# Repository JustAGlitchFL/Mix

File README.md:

# Mix
A multipurpose audio-focused console

## Why
I find myself constantly tuning my audio mix from different apps through windows, and would like a panel to adjust levels on the fly. I also wanted to use this for mixing audio for music and video projects, so I included 8 channels. Each channel has a slider for feed volume, an encoder for monitoring volume, a solo button, and a mute button. Everything is remappable to select functions for your usecase. I also included 2 neopixels per channel, one for status, and one for leveling by color.

## Assembly
Like [Timeline](https://github.com/justaglitchfl/timeline), ~~no case for this one~~ CASE FILES AVAILABLE NOW, as I want that raw PCB aesthetic. Solder everything together, good luck with the SMD for the ADC and IO expander! Might do a case when I get to uni and have access to actually functional printers if I get tired of the pcb as is. As with my other projects recently, drop some 3M 2229 on the back to protect it/the table, and to keep it in place (I love this stuff).

## BOM
|q  |part                          |link                                                                                                                                                                                                                                                                                                                                                                                                                                                                                                                |price       |total  |
|---|------------------------------|--------------------------------------------------------------------------------------------------------------------------------------------------------------------------------------------------------------------------------------------------------------------------------------------------------------------------------------------------------------------------------------------------------------------------------------------------------------------------------------------------------------------|------------|-------|
|1  |pcb                           |                                                                                                                                                                                                                                                                                                                                                                                                                                                                                                                    |$42.60      |$128.78|
|16 |switches                      |https://www.amazon.com/Kailh-Box-Switches-Mechanical-Keyboards/dp/B09WYVJ4F9/ref=sr_1_6?crid=2BTWSUBF3M8FT&dib=eyJ2IjoiMSJ9.E7vTxhYXmILeUbyObROhU1-pIkGjrufbSlMHAIG1e1llnfgUb6kJH0aZrhKnghy3-ae39fOUC746uLoqyr3XWC62Htlj0ggtZ9ec4c0ypx7s1OXmhTfKQ-o2rJuyfk5aXhqV22nhrib2PZU7WaA4AQrzeExJuEfAlETDZ-vuRMSWAneuQMiuWeqVX5Q3DunrHOugdER5ro68nIeODJWdx1rM1AFtYghjvFvBt4W0Gkk.dJo-mbx2UtVbx1mbN98GCLOOPWtmLr-b0G6qjvDffpM&dib_tag=se&keywords=kailh%2Bbox%2Bjade&qid=1754458378&sprefix=kailh%2Bbo%2Caps%2C137&sr=8-6&th=1|$25.98      |       |
|8  |ECE11                         |https://lcsc.com/product-detail/Rotary-Encoders_ALPSALPINE-EC11E18244AU_C202365.html                                                                                                                                                                                                                                                                                                                                                                                                                                |$15.71      |       |
|8  |slide potentiometer           |https://lcsc.com/product-detail/Potentiometers-Variable-Resistors_BOURNS-PTA4543-2015DPB103_C17444183.html?s_z=n_%25C2%25B120%2525%2520250mW%252010k%25CE%25A9%2520Through%2520Hole%2520Potentiometers%252C%2520Variable%2520Resistors%2520ROHS                                                                                                                                                                                                                                                                     |$14.16      |       |
|1  |MCP23017_SO                   |https://lcsc.com/product-detail/I-O-Expanders_MICROCHIP-MCP23017T-E-SO_C629440.html?s_z=n_MCP23017_SO                                                                                                                                                                                                                                                                                                                                                                                                               |$1.94       |       |
|1  |MCP3008                       |https://lcsc.com/product-detail/Analog-to-Digital-Converters-ADC_MICROCHIP-MCP3008T-I-SL_C2651321.html?s_z=n_mcp3008                                                                                                                                                                                                                                                                                                                                                                                                |$3.30       |       |
|16 |0805 signal diode             |                                                                                                                                                                                                                                                                                                                                                                                                                                                                                                                    |have on hand|       |
|16 |sk6812 mini e                 |                                                                                                                                                                                                                                                                                                                                                                                                                                                                                                                    |have on hand|       |
|1  |pi pico usbc (i wan orph pico)|https://www.aliexpress.us/item/3256807183354679.html?spm=a2g0o.productlist.main.5.7a7f3de52hAPEA&algo_pvid=1f0d5b04-b26a-48e7-9a46-02294e034b27&algo_exp_id=1f0d5b04-b26a-48e7-9a46-02294e034b27-4&pdp_ext_f=%7B%22order%22%3A%2284%22%2C%22eval%22%3A%221%22%7D&pdp_npi=4%40dis%21USD%212.56%212.56%21%21%212.56%212.56%21%402101ef5e17540194226302590e807a%2112000040462155654%21sea%21US%216129401916%21X&curPageLogUid=bwr0jMqPdQNe&utparam-url=scene%3Asearch%7Cquery_from%3A                                  |$3.56       |       |
|1  |lcsc s+h                      |                                                                                                                                                                                                                                                                                                                                                                                                                                                                                                                    |$21.53      |       |

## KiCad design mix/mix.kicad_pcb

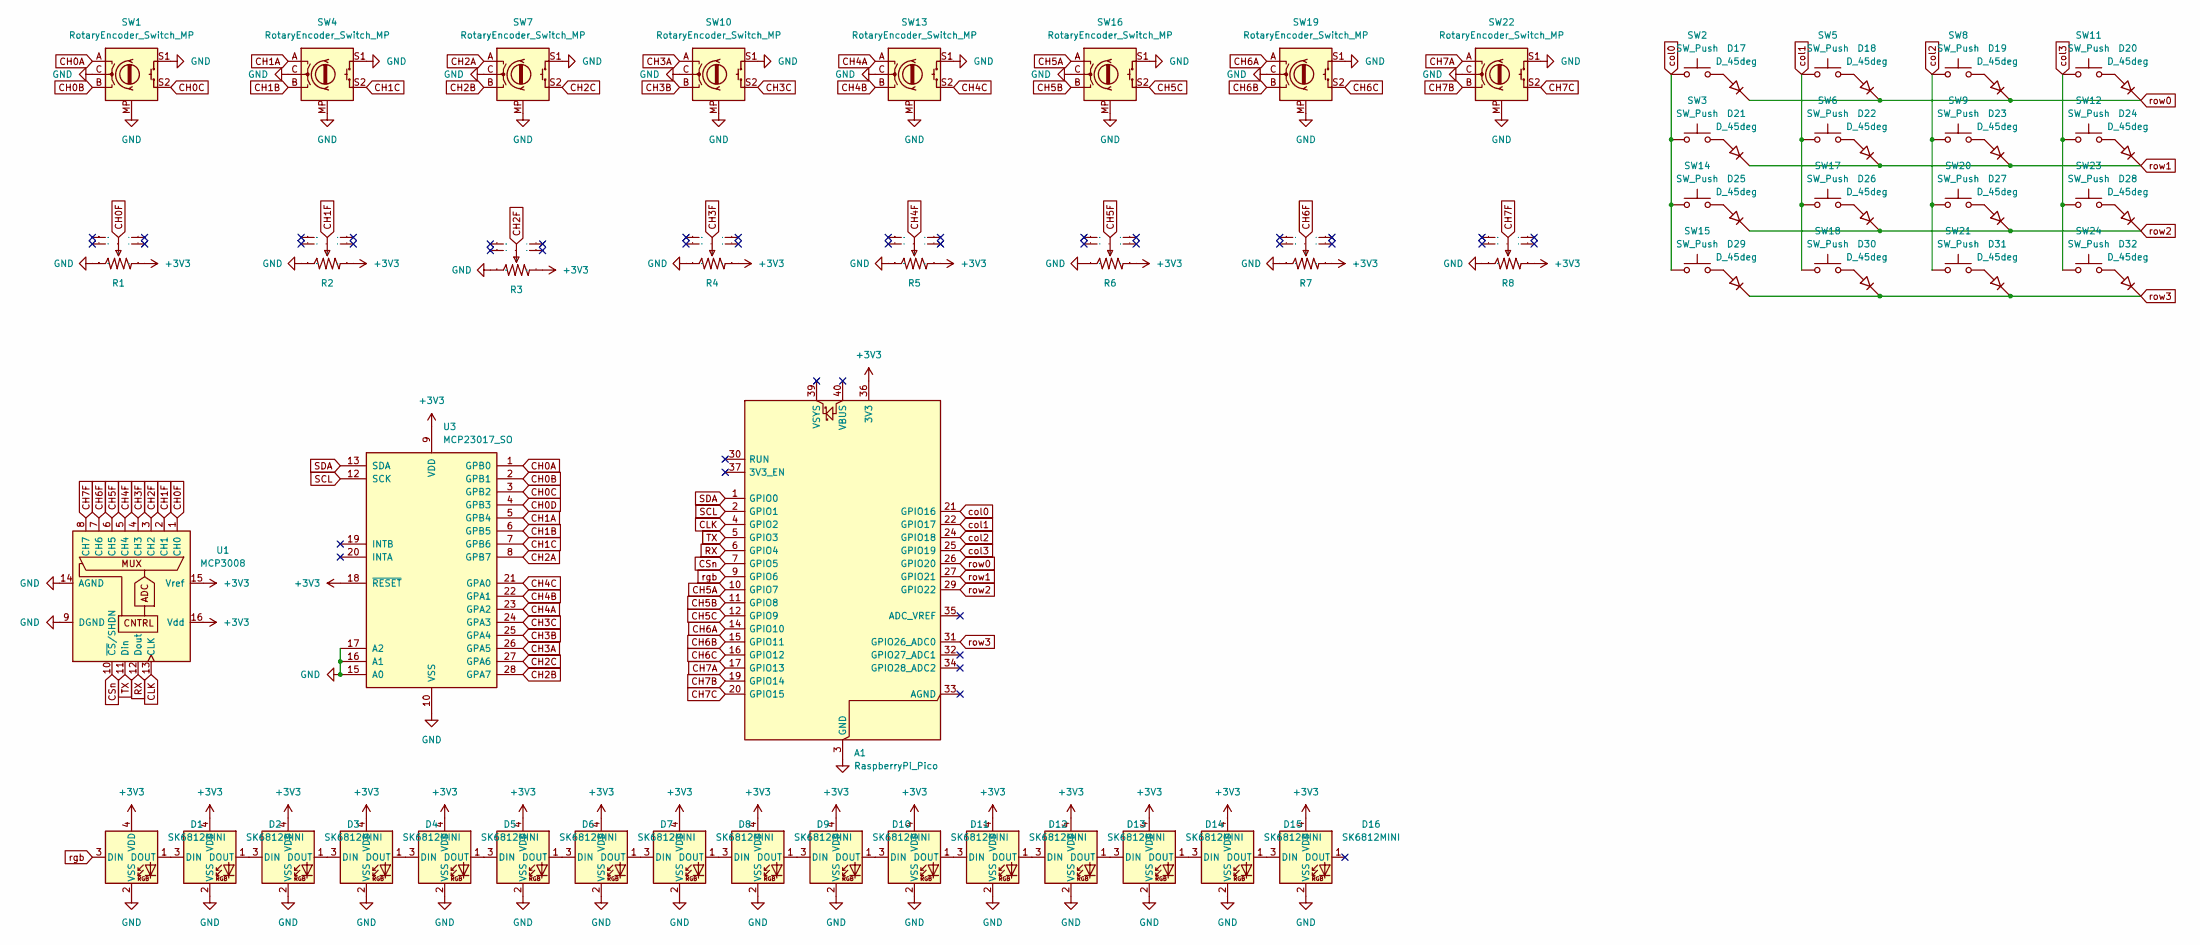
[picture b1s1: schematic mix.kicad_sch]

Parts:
A1: RaspberryPi_Pico; RaspberryPi_Pico_Common_Unspecified
D1, D2, D3, D4, D5, D6, D7, D8, D9, D10, D11, D12, D13, D14, D15, D16: SK6812MINI; SK6812MINI-E
D17, D18, D19, D20, D21, D22, D23, D24, D25, D26, D27, D28, D29, D30, D31, D32: D_45deg; D_0805_2012Metric_Pad1.15x1.40mm_HandSolder
R1, R2, R3, R4, R5, R6, R7, R8: RES-ADJ_PTA4543-2015CPB102
SW1, SW4, SW7, SW10, SW13, SW16, SW19, SW22: RotaryEncoder_Switch_MP; RotaryEncoder_Alps_EC11E-Switch_Vertical_H20mm_MountingHoles
SW2, SW3, SW5, SW6, SW8, SW9, SW11, SW12, SW14, SW15, SW17, SW18, SW20, SW21, SW23, SW24: SW_Push; SW_Cherry_MX_1.00u_PCB
U1: MCP3008; SOIC-16_3.9x9.9mm_P1.27mm
U3: MCP23017_SO; SOIC-28W_7.5x17.9mm_P1.27mm

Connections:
+3V3: A1.36 (3V3), D1.4 (VDD), D2.4 (VDD), D3.4 (VDD), D4.4 (VDD), D5.4 (VDD), D6.4 (VDD), D7.4 (VDD), D8.4 (VDD), D9.4 (VDD), D10.4 (VDD), D11.4 (VDD), D12.4 (VDD), D13.4 (VDD), D14.4 (VDD), D15.4 (VDD), D16.4 (VDD), R1.3, R2.3, R3.3, R4.3, R5.3, R6.3, R7.3, R8.3, U1.15 (Vref), U1.16 (Vdd), U3.9 (VDD), U3.18 (~RESET)
CH0A: SW1.A, U3.1 (GPB0)
CH0B: SW1.B, U3.2 (GPB1)
CH0C: SW1.S2, U3.3 (GPB2)
CH0D: U3.4 (GPB3)
CH0F: R1.2, U1.1 (CH0)
CH1A: SW4.A, U3.5 (GPB4)
CH1B: SW4.B, U3.6 (GPB5)
CH1C: SW4.S2, U3.7 (GPB6)
CH1F: R2.2, U1.2 (CH1)
CH2A: SW7.A, U3.8 (GPB7)
CH2B: SW7.B, U3.28 (GPA7)
CH2C: SW7.S2, U3.27 (GPA6)
CH2F: R3.2, U1.3 (CH2)
CH3A: SW10.A, U3.26 (GPA5)
CH3B: SW10.B, U3.25 (GPA4)
CH3C: SW10.S2, U3.24 (GPA3)
CH3F: R4.2, U1.4 (CH3)
CH4A: SW13.A, U3.23 (GPA2)
CH4B: SW13.B, U3.22 (GPA1)
CH4C: SW13.S2, U3.21 (GPA0)
CH4F: R5.2, U1.5 (CH4)
CH5A: A1.10 (GPIO7), SW16.A
CH5B: A1.11 (GPIO8), SW16.B
CH5C: A1.12 (GPIO9), SW16.S2
CH5F: R6.2, U1.6 (CH5)
CH6A: A1.14 (GPIO10), SW19.A
CH6B: A1.15 (GPIO11), SW19.B
CH6C: A1.16 (GPIO12), SW19.S2
CH6F: R7.2, U1.7 (CH6)
CH7A: A1.17 (GPIO13), SW22.A
CH7B: A1.19 (GPIO14), SW22.B
CH7C: A1.20 (GPIO15), SW22.S2
CH7F: R8.2, U1.8 (CH7)
CLK: A1.4 (GPIO2), U1.13 (CLK)
CSn: A1.7 (GPIO5), U1.10 (~CS/SHDN)
GND: A1.3 (GND), A1.8 (GND), A1.13 (GND), A1.18 (GND), A1.23 (GND), A1.28 (GND), A1.38 (GND), D1.2 (VSS), D2.2 (VSS), D3.2 (VSS), D4.2 (VSS), D5.2 (VSS), D6.2 (VSS), D7.2 (VSS), D8.2 (VSS), D9.2 (VSS), D10.2 (VSS), D11.2 (VSS), D12.2 (VSS), D13.2 (VSS), D14.2 (VSS), D15.2 (VSS), D16.2 (VSS), R1.1, R2.1, R3.1, R4.1, R5.1, R6.1, R7.1, R8.1, SW1.C, SW1.MP, SW1.S1, SW4.C, SW4.MP, SW4.S1, SW7.C, SW7.MP, SW7.S1, SW10.C, SW10.MP, SW10.S1, SW13.C, SW13.MP, SW13.S1, SW16.C, SW16.MP, SW16.S1, SW19.C, SW19.MP, SW19.S1, SW22.C, SW22.MP, SW22.S1, U1.9 (DGND), U1.14 (AGND), U3.10 (VSS), U3.15 (A0), U3.16 (A1), U3.17 (A2)
unnamed: D1.1 (DOUT), D2.3 (DIN)
unnamed: D2.1 (DOUT), D3.3 (DIN)
unnamed: D3.1 (DOUT), D4.3 (DIN)
unnamed: D4.1 (DOUT), D5.3 (DIN)
unnamed: D5.1 (DOUT), D6.3 (DIN)
unnamed: D6.1 (DOUT), D7.3 (DIN)
unnamed: D7.1 (DOUT), D8.3 (DIN)
unnamed: D8.1 (DOUT), D9.3 (DIN)
unnamed: D9.1 (DOUT), D10.3 (DIN)
unnamed: D10.1 (DOUT), D11.3 (DIN)
unnamed: D11.1 (DOUT), D12.3 (DIN)
unnamed: D12.1 (DOUT), D13.3 (DIN)
unnamed: D13.1 (DOUT), D14.3 (DIN)
unnamed: D14.1 (DOUT), D15.3 (DIN)
unnamed: D15.1 (DOUT), D16.3 (DIN)
unnamed: D17.2 (A), SW2.2
unnamed: D18.2 (A), SW5.2
unnamed: D19.2 (A), SW8.2
unnamed: D20.2 (A), SW11.2
unnamed: D21.2 (A), SW3.2
unnamed: D22.2 (A), SW6.2
unnamed: D23.2 (A), SW9.2
unnamed: D24.2 (A), SW12.2
unnamed: D25.2 (A), SW14.2
unnamed: D26.2 (A), SW17.2
unnamed: D27.2 (A), SW20.2
unnamed: D28.2 (A), SW23.2
unnamed: D29.2 (A), SW15.2
unnamed: D30.2 (A), SW18.2
unnamed: D31.2 (A), SW21.2
unnamed: D32.2 (A), SW24.2
RX: A1.6 (GPIO4), U1.12 (Dout)
SCL: A1.2 (GPIO1), U3.12 (SCK)
SDA: A1.1 (GPIO0), U3.13 (SDA)
TX: A1.5 (GPIO3), U1.11 (Din)
col0: A1.21 (GPIO16), SW2.1, SW3.1, SW14.1, SW15.1
col1: A1.22 (GPIO17), SW5.1, SW6.1, SW17.1, SW18.1
col2: A1.24 (GPIO18), SW8.1, SW9.1, SW20.1, SW21.1
col3: A1.25 (GPIO19), SW11.1, SW12.1, SW23.1, SW24.1
rgb: A1.9 (GPIO6), D1.3 (DIN)
row0: A1.26 (GPIO20), D17.1 (K), D18.1 (K), D19.1 (K), D20.1 (K)
row1: A1.27 (GPIO21), D21.1 (K), D22.1 (K), D23.1 (K), D24.1 (K)
row2: A1.29 (GPIO22), D25.1 (K), D26.1 (K), D27.1 (K), D28.1 (K)
row3: A1.31 (GPIO26_ADC0), D29.1 (K), D30.1 (K), D31.1 (K), D32.1 (K)

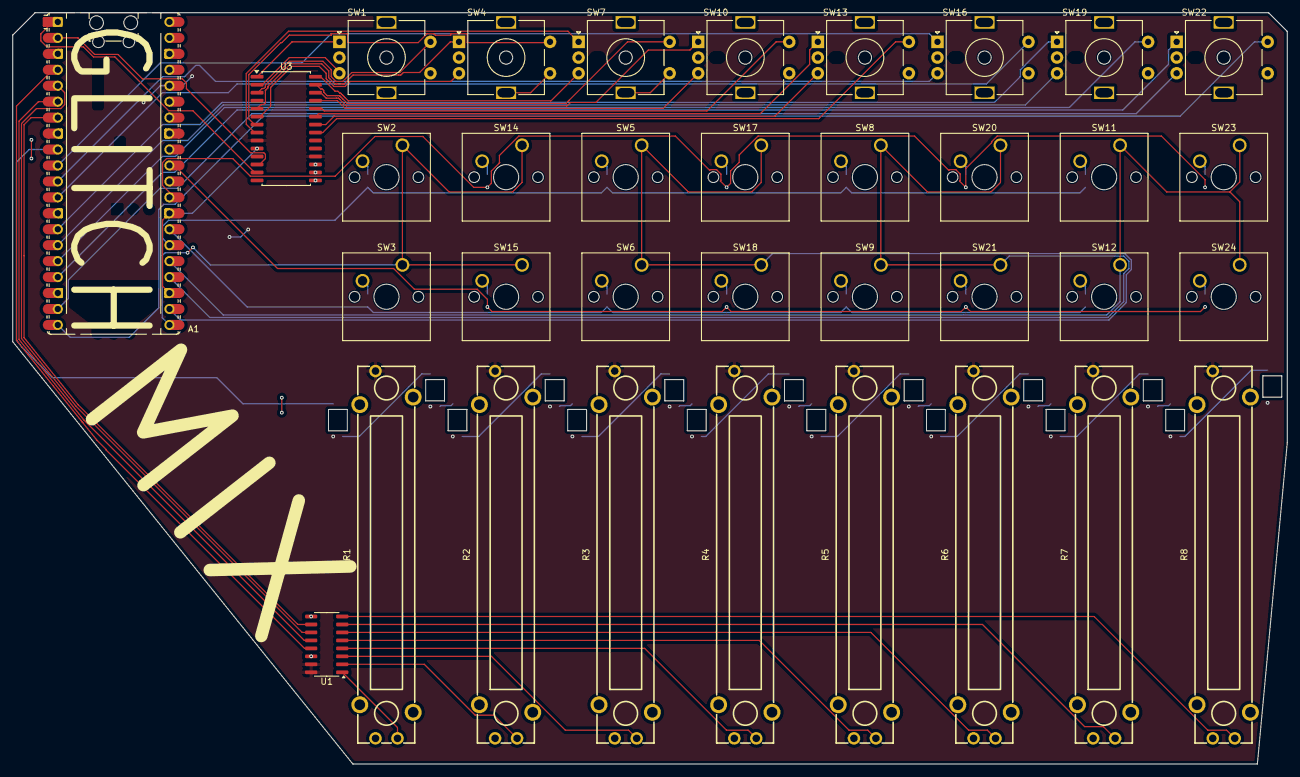
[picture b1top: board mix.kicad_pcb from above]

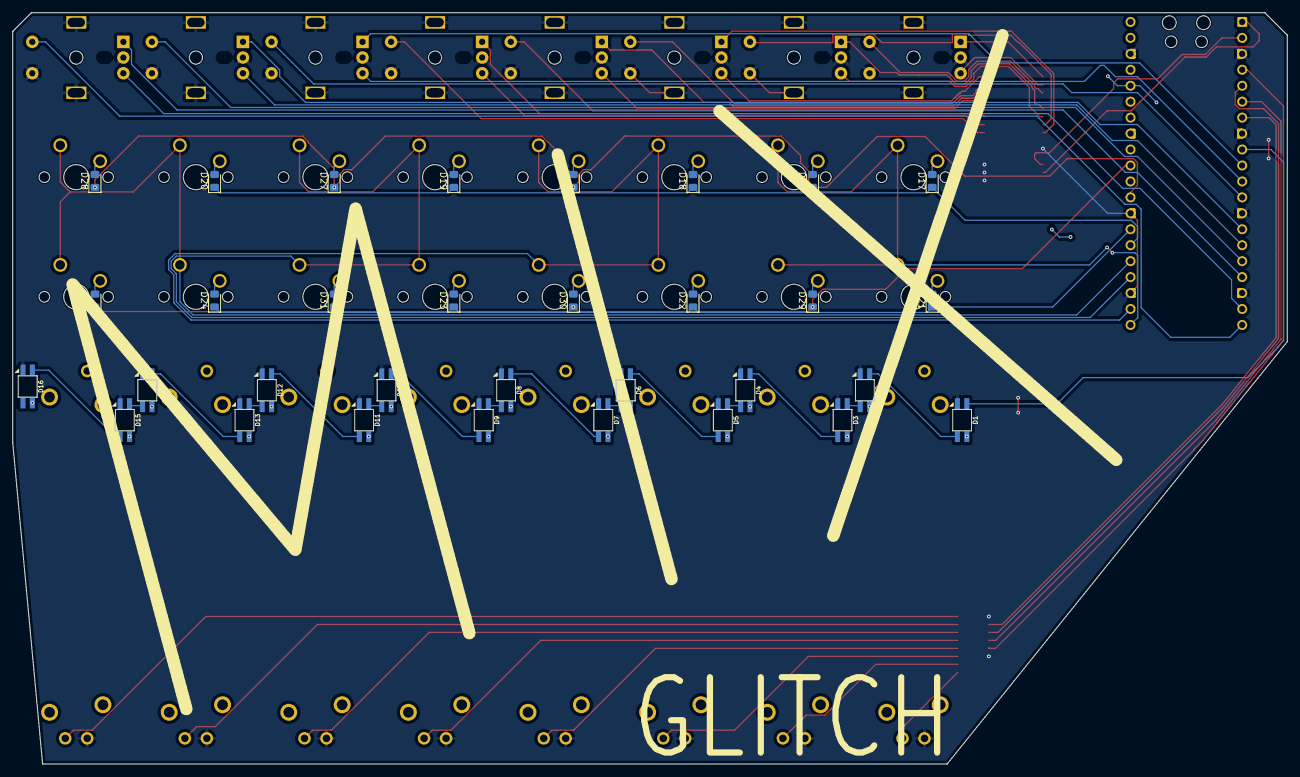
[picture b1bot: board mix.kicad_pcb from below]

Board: 2 copper layers, 202.9 x 119.6 mm, 67 parts (32 on the bottom side), 80 nets.

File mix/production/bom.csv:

Designator,Footprint,Quantity,Value,LCSC Part #
A1,RaspberryPi_Pico_Common_Unspecified,1,RaspberryPi_Pico,
"D1, D10, D11, D12, D13, D14, D15, D16, D2, D3, D4, D5, D6, D7, D8, D9",SK6812MINI-E,16,SK6812MINI,
"D17, D18, D19, D20, D21, D22, D23, D24, D25, D26, D27, D28, D29, D30, D31, D32",0805,16,D_45deg,
"R1, R2, R3, R4, R5, R6, R7, R8",RES-ADJ_PTA4543-2015CPB102,8,~,
"SW1, SW10, SW13, SW16, SW19, SW22, SW4, SW7",RotaryEncoder_Alps_EC11E-Switch_Vertical_H20mm_MountingHoles,8,RotaryEncoder_Switch_MP,
"SW11, SW12, SW14, SW15, SW17, SW18, SW2, SW20, SW21, SW23, SW24, SW3, SW5, SW6, SW8, SW9",SW_Cherry_MX_1.00u_PCB,16,SW_Push,
U1,SOIC-16_3.9x9.9mm_P1.27mm,1,MCP3008,
U3,SOIC-28W_7.5x17.9mm_P1.27mm,1,MCP23017_SO,

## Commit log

2025-07-21 sync
2025-07-22 jgfk;j
2025-08-01 images
2025-08-04 firmware
2025-08-06 case+fw
2025-08-06 Update BOM
2025-08-06 update bom csv
